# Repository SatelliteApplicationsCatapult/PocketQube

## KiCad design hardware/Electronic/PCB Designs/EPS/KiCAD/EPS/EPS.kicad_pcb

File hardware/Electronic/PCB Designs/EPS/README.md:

# PQ60 Electrical Power System

### At a glance
The current EPS design features the following basic systems:

1. Four _IXYS_ solar panels as a power source

2. Two _LTC3105_ based MPPT circuits to maximise the solar power generated

3. A _MAX8606ETD_ charge management IC to facilitate safe battery charging and effective system load management.

4. A regulation circuit including:
	* A watchdog timer to detect unresponsive MCUs (_STWD100PYW83F_)
	* A brownout monitor to detect invalid voltages (_BU4231G-TR_)
	* A 3V3 LDO regulator with active-high enable, allowing supervisor ICs or external MCUs to trigger a reset (_MIC5353-3.3YMT_)
	
5. Current monitoring:
	* _FAN4010IL6X_F113_ based high-side unidirectional current sense amplifier ICs to monitor solar output, total 3V3 draw and draw from the battery voltage line on the PQ60 bus
	* _INA211A_ based high-side bi-directional current sense amplifier to monitor total current draw and supply to the battery
	
6. Voltage monitoring:
	* Two MOSFET switched divider networks to measure the MPPT output voltage, the raw battery voltage
	* Direct measurement through MCU ADC of the 3V3 bus voltage
	
7. A 650mAh 3.7V single cell lithium polymer battery

8. Five high-side MOSFET (_NTA4151P & FK3303010L_) switched lines for the __PQ60__ standard, three 3V3 and two raw battery voltage. Each line is reverse polarity protected by the MOSFET and over current protected by a resettable polyfuse (_1206L025YR_)

9. A single _MKL02Z32VFM4_ 32 bit Kinetis MCU, for power management, current and voltage monitoring, line switching and communication with the OBC through I2C

### Usage
Will write something in this section once we actually have an EPS and some code to go with it. Maybe unnecessary if all dealt with through cube library? Will list maximum ratings, tolerances and so on.

### Current design
The current revision of the EPS board uses four __IXYS__ solar panels (_SLMD121H10L-ND_) as a power source, or can also be charged from a standard USB supply. The board contains two Maximum Power Point Tracker (MPPT) circuits based on the __LTC3105__ (_LTC3105EDD#PBF_) DC-DC switching boost regulator, sharing two panels each, with a low forward voltage drop schottkey diode to prevent reverse current leakage from the panels while not illuminated. The output of the MPPT circuits is fed through a twin channel MOSFET based ideal diode IC (_LTC4413_) to the charge management IC (_MAX8606ETD+T_). The total current produced by the MPPT circuits and delivered to the charging IC is monitored by a high side current sense amplifier (_FAN4010IL6X_), and the supply voltage can be measured through a resistor divider network. A MOSFET exists (_NX7002AK_) to disable this divider circuit to prevent current draw when not required. The charge management IC includes integrated load servicing. When the battery voltage exceeds 3.5V, the system output will be internally connected to the battery. Below this voltage, the power supply to the IC will first be used to service the system load, with the remaining available current being used to charge the battery. Both charging sources, the MPPTs and the USB supply, can be disabled if required, in order to obtain accurate battery voltage measurements. The MPPTs can be disabled through a signal to the SHDN input, and the USB supply is connected through a high side switched MOSFET circuit to enable disconnecting. The SHDN signal to the _LTC3105_ MPPTs is connected through an opto-isolator to allow recovery in the event of a fully discharged battery.

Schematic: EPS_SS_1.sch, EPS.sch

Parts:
C1, C2, C4, C5, C6, C8: 10uF; RESISTOR_C0603
C3, C7: 1uF; RESISTOR_C0402
IND1, IND2: WE-TPC-744031100; UBO_PQ60_WE-TPC-744031100
MPPT1, MPPT2: LTC3105; UBO_PQ60_DFN-3X3
R1, R4: 1.3M; RESISTOR_R0402
R2, R5: 330K; RESISTOR_R0402
R3, R6: 501K; RESISTOR_R0402
R33: 150R; RESISTOR_R0402
SOL1, SOL2, SOL3, SOL4: JST-B2B-ZH; UBO_PQ60_JST-B2B-ZR
U1: LTC4413EDDPBF; UBO_PQ60_DFN300X300X80-11N
U$4, U$10, U$14, U$17, U$31, U$32: BAT41; UBO_PQ60_SOD-123
U$24: EL3H7; UBO_PQ60_EL3H7

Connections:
GND: C1.2, C2.2, C3.2, C4.2, C5.2, C6.2, C7.2, C8.2, MPPT1.3 (FBLDO), MPPT1.EXP (GND), MPPT2.3 (FBLDO), MPPT2.EXP (GND), R2.1, R3.2, R5.1, R6.2, SOL1.P$1 (-), SOL2.P$1 (-), SOL3.P$1 (-), SOL4.P$1 (-), U1.2 (ENBA), U1.3 (GND), U1.4 (ENBB), U1.9 (STAT), U1.11 (EP), U$24.CATH (CATHODE), U$24.EMIT (EMITTER); also elsewhere on the board
MPPT1: C2.1, MPPT1.9 (VOUT), R1.2, U1.1 (INA)
MPPT2: C6.1, MPPT2.9 (VOUT), R4.2, U1.5 (INB)
MPPT_RAW: U1.6 (OUTB), U1.10 (OUTA); also elsewhere on the board
unnamed: IND1.P$1 (1), MPPT1.7 (SW)
unnamed: C1.1, IND1.P$3 (2), MPPT1.6 (VIN), U$31.P$1 (C), U$32.P$1 (C)
unnamed: IND2.P$1 (1), MPPT2.7 (SW)
unnamed: C3.1, MPPT1.10 (AUX)
unnamed: C7.1, MPPT2.10 (AUX)
unnamed: C5.1, IND2.P$3 (2), MPPT2.6 (VIN), U$14.P$1 (C), U$17.P$1 (C)
unnamed: MPPT2.1 (FB), R4.1, R5.2
unnamed: C4.1, MPPT1.2 (LDO)
unnamed: MPPT1.1 (FB), R1.1, R2.2
unnamed: MPPT2.5 (MPPC), R6.1
unnamed: C8.1, MPPT2.2 (LDO)
unnamed: MPPT2.4 (SHDN), U$10.P$2 (A)
unnamed: SOL4.P$2 (+), U$17.P$2 (A)
unnamed: MPPT1.4 (SHDN), U$4.P$2 (A)
unnamed: MPPT1.5 (MPPC), R3.1
unnamed: SOL3.P$2 (+), U$14.P$2 (A)
unnamed: SOL2.P$2 (+), U$31.P$2 (A)
unnamed: SOL1.P$2 (+), U$32.P$2 (A)
unnamed: R33.2, U$24.ANOD (ANODE)
OPTO: R33.1; also elsewhere on the board
SHDN: U$4.P$1 (C), U$10.P$1 (C), U$24.COLL (COLLECTOR)

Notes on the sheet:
10uH
501K --> 5.01V MPPV
1.004Vx((1.3M/330K)+1) =~4.959Vout
Maxmimu Power Point Tracking circuits, Opto-isolated charge disable and dual ideal diode outputs

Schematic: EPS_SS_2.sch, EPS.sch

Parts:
BAT56: JST-B2B-ZH; UBO_PQ60_JST-B2B-ZR
BU4331G-TR56: BU4231G-TR; EPS_PQ60_SSOP5
C21: 10nF; RESISTOR_C0402
C22: 1uF; RESISTOR_C0402
C23: 1nF; RESISTOR_C0402
INA210AIDCKT56: INA211A; UBO_PQ60_SC-70
PWR56: 961102-5604-AR; UBO_PQ60_961102-5604-AR
R7, R8, R9, R10, R15, R20, R21, R24, R28: 10K; RESISTOR_R0402
R13, R22, R36, R37: 0.15R, 1%; RESISTOR_R0603
R16: 2.2K; RESISTOR_R0402
R17: 3.3K; RESISTOR_R0402
R19: 0.015R 1%; RESISTOR_R0603
R40: 47K; RESISTOR_R0402
SJ1: UBO_PQ60_SJ
STWD100PYW83F56: STWD100PYW83F; UBO_PQ60_SOT_323-5
U9: TPS2553DRVT; UBO_PQ60_SON65P200X200X80-7N
U$2: BQ24079; UBO_PQ60_PVQFN16-THERM
U$15: PMV40UN2; UBO_PQ60_SOT23-3
U$18, U$19, U$25, U$26: FAN4010IL6X_F113; UBO_PQ60_FAN4010IL6X_F113
U$20: NCP706AMX300TAG; UBO_PQ60_XDFN8

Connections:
+3V3: INA210AIDCKT56.3 (VCC), R20.2, R36.2, U$25.6 (LOAD); also elsewhere on the board
+3V3_ISEN: R10.2, U$25.3 (IOUT); also elsewhere on the board
+3V3_REG: R36.1, R37.1, U$20.P$1 (OUT), U$20.P$2 (OUT), U$20.P$4 (SNS), U$25.1 (VIN), U$26.1 (VIN)
+3V3_SW: R37.2, U$26.6 (LOAD); also elsewhere on the board
+3V3_SW_ISEN: R9.2, U$26.3 (IOUT); also elsewhere on the board
BATV_BUS: R22.1, U$19.6 (LOAD); also elsewhere on the board
BAT_BUS_ISEN: R7.1, U$19.3 (IOUT); also elsewhere on the board
BAT_RAW_ISEN: INA210AIDCKT56.6 (OUT); also elsewhere on the board
BAT_RAW_ISEN_EN: U$15.1 (G); also elsewhere on the board
CHG_INPUT: R13.2, U$2.6 (EN1), U$2.13 (IN), U$18.6 (LOAD); also elsewhere on the board
EN: BU4331G-TR56.1 (VOUT), C23.1, R28.1, STWD100PYW83F56.1 (WDO), U9.4 (EN), U$20.P$6 (EN); also elsewhere on the board
GND: BAT56.P$1 (-), BU4331G-TR56.3 (GND), C21.2, C22.2, C23.2, INA210AIDCKT56.2 (GND), R7.2, R8.1, R9.1, R10.1, R15.1, R16.1, R17.1, R24.1, R40.1, STWD100PYW83F56.2 (GND), U9.5 (GND), U9.7 (EP), U$2.4 (CE), U$2.5 (EN2), U$2.7 (PGOOD), U$2.8 (VSS), U$2.9 (CHG), U$2.14 (TMR), U$2.15 (SYSOFF), U$2.17 (VSS), U$15.2 (S), U$18.5 (GND), U$19.5 (GND), U$20.P$5 (GND), U$20.P$9 (GND), U$25.5 (GND), U$26.5 (GND); also elsewhere on the board
MPPT_RAW: R13.1, U$18.1 (VIN); also elsewhere on the board
unnamed: INA210AIDCKT56.4 (IN+), R19.2, U$2.2 (BAT), U$2.3 (BAT)
unnamed: R15.2, U$2.1 (TS)
unnamed: R16.2, U$2.16 (ISET)
unnamed: R17.2, U$2.12 (ILIM)
unnamed: BAT56.P$2 (+), INA210AIDCKT56.5 (IN-), R19.1, R22.2, U$19.1 (VIN)
unnamed: R21.1, U$15.3 (D)
unnamed: INA210AIDCKT56.1 (REF), R20.1, R21.2
unnamed: BU4331G-TR56.5 (CT), C21.1
unnamed: R24.2, SJ1.2, STWD100PYW83F56.3 (EN)
unnamed: R40.2, U9.2 (ILIM)
SOL_ISEN: R8.2, U$18.3 (IOUT); also elsewhere on the board
SYS: PWR56.PIN2, U$2.10 (OUT), U$2.11 (OUT)
SYS_RAW: SJ1.1, U9.1 (OUT), U$20.P$7 (IN), U$20.P$8 (IN)
SYS_SW: BU4331G-TR56.2 (VDD), C22.1, PWR56.PIN1, R28.2, STWD100PYW83F56.5 (VCC), U9.6 (IN)
WDI: STWD100PYW83F56.4 (WDI); also elsewhere on the board

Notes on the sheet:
Panasonic ERJ3RSFR15V
200mA --> 3V
SUSUMU RR0816P-103-B-T5
VISHAY WSL0805R0300FEA
Total battery current monitoring
charge / discharge
INA210 200 gain 1.5V = A 3V = +500mA 0V = -500mA
Current monitoring on raw battery line
Main systems load
3v3 total bus load
~500mA limit
Watchdog timer Solder bridge to disable
Brownout monitor Vout high when valid voltage source detected
MOSFET load switch
3.0V 1.5A LDO
2.2K --> 405mA charge limit
3.3K --> 470mA input limit
Thermistor input

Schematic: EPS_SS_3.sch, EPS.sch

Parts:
C25, C26: 1uF; RESISTOR_C0402
FD1, FD2, FD3, FD4: FIDUCIAL; ADAFRUIT_FIDUCIAL_1MM
PQ60_HEADER56: FX8C-060P-SV2(92); OBC_FX8C-060P-SV(92)
PQ60_RECEPTACLE56: FX8C-060S-SV(92); TEMPLATE_FX8C-060S-SV(92)
R18, R25, R26, R27, R30: 10K; RESISTOR_R0402
TP1: TPTP07R; TESTPAD_TP07R
U10, U11, U12: TPS22960DCNR; UBO_PQ60_SOT65P280X145-8N
U$1, U$5, U$6, U$7: 3MMPILAR; UBO_PQ60_3MMPILAR
U$3, U$16, U$23, U$27, U$28: DEBUG-TP; UBO_PQ60_DEBUG-TP
U$8: ABS25_32.768KHZ; UBO_PQ60_ABS25
U$11, U$12: PMV40UN2; UBO_PQ60_SOT23-3
U$21: MKL02Z16VFM4; OBC_MKL02Z16VFM4
U$22: TAG_CONNECT; UBO_PQ60_TAG_CONNECT

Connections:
+3V3: C25.1, C26.1, PQ60_HEADER56.P$57, PQ60_HEADER56.P$58, PQ60_HEADER56.P$59, PQ60_HEADER56.P$60, PQ60_RECEPTACLE56.P$57, PQ60_RECEPTACLE56.P$58, PQ60_RECEPTACLE56.P$59, PQ60_RECEPTACLE56.P$60, U$3.P$1, U$21.3 (VDD), U$21.4 (VREFH), U$22.1 (VCC); also elsewhere on the board
+3V3_ISEN: U$21.16 (PTB0); also elsewhere on the board
+3V3_SW: U10.1 (VIN1), U10.4 (VIN2), U11.4 (VIN2); also elsewhere on the board
+3V3_SW1: PQ60_HEADER56.P$1, PQ60_HEADER56.P$2, PQ60_RECEPTACLE56.P$1, PQ60_RECEPTACLE56.P$2, U10.5 (VOUT2)
+3V3_SW1_EN: U10.3 (ON2), U$21.18 (PTB2)
+3V3_SW2: PQ60_HEADER56.P$5, PQ60_HEADER56.P$6, PQ60_RECEPTACLE56.P$5, PQ60_RECEPTACLE56.P$6, U10.8 (VOUT1)
+3V3_SW2_EN: U10.2 (ON1), U$21.19 (PTA8)
+3V3_SW3: PQ60_HEADER56.P$9, PQ60_HEADER56.P$10, PQ60_RECEPTACLE56.P$9, PQ60_RECEPTACLE56.P$10, U11.5 (VOUT2)
+3V3_SW3_EN: U11.3 (ON2), U$21.20 (PTA9)
+3V3_SW_ISEN: U$21.15 (PTA7); also elsewhere on the board
+5V_USB: PQ60_HEADER56.P$21, PQ60_HEADER56.P$22, PQ60_RECEPTACLE56.P$21, PQ60_RECEPTACLE56.P$22, R30.2, U12.1 (VIN1)
BATV_BUS: PQ60_HEADER56.P$49, PQ60_HEADER56.P$50, PQ60_HEADER56.P$51, PQ60_HEADER56.P$52, PQ60_RECEPTACLE56.P$49, PQ60_RECEPTACLE56.P$50, PQ60_RECEPTACLE56.P$51, PQ60_RECEPTACLE56.P$52, R18.2, U11.1 (VIN1), U12.4 (VIN2); also elsewhere on the board
BATV_SENS: R18.1, R25.2, U$21.25 (PTB5)
BATV_SENS_EN: U$11.1 (G), U$21.27 (PTA13)
BATV_SW1: PQ60_HEADER56.P$13, PQ60_HEADER56.P$14, PQ60_RECEPTACLE56.P$13, PQ60_RECEPTACLE56.P$14, U11.8 (VOUT1)
BATV_SW1_EN: U11.2 (ON1), U$21.21 (PTA10)
BATV_SW2: PQ60_HEADER56.P$17, PQ60_HEADER56.P$18, PQ60_RECEPTACLE56.P$17, PQ60_RECEPTACLE56.P$18, U12.5 (VOUT2)
BATV_SW2_EN: U12.3 (ON2), U$21.22 (PTA11)
BAT_BUS_ISEN: U$21.11 (PTB8); also elsewhere on the board
BAT_RAW_ISEN: U$21.12 (PTB9); also elsewhere on the board
BAT_RAW_ISEN_EN: U$21.14 (PTB11); also elsewhere on the board
CHG_INPUT: U12.8 (VOUT1); also elsewhere on the board
EN: PQ60_HEADER56.P$27, PQ60_RECEPTACLE56.P$27; also elsewhere on the board
EXTAL: U$8.1, U$21.7 (PTA3)
GND: C25.2, C26.2, PQ60_HEADER56.P$3, PQ60_HEADER56.P$4, PQ60_HEADER56.P$7, PQ60_HEADER56.P$8, PQ60_HEADER56.P$11, PQ60_HEADER56.P$12, PQ60_HEADER56.P$15, PQ60_HEADER56.P$16, PQ60_HEADER56.P$19, PQ60_HEADER56.P$20, PQ60_HEADER56.P$23, PQ60_HEADER56.P$24, PQ60_HEADER56.P$28, PQ60_HEADER56.P$45, PQ60_HEADER56.P$46, PQ60_HEADER56.P$47, PQ60_HEADER56.P$48, PQ60_HEADER56.P$53, PQ60_HEADER56.P$54, PQ60_HEADER56.P$55, PQ60_HEADER56.P$56, PQ60_RECEPTACLE56.P$3, PQ60_RECEPTACLE56.P$4, PQ60_RECEPTACLE56.P$7, PQ60_RECEPTACLE56.P$8, PQ60_RECEPTACLE56.P$11, PQ60_RECEPTACLE56.P$12, PQ60_RECEPTACLE56.P$15, PQ60_RECEPTACLE56.P$16, PQ60_RECEPTACLE56.P$19, PQ60_RECEPTACLE56.P$20, PQ60_RECEPTACLE56.P$23, PQ60_RECEPTACLE56.P$24, PQ60_RECEPTACLE56.P$28, PQ60_RECEPTACLE56.P$45, PQ60_RECEPTACLE56.P$46, PQ60_RECEPTACLE56.P$47, PQ60_RECEPTACLE56.P$48, PQ60_RECEPTACLE56.P$53, PQ60_RECEPTACLE56.P$54, PQ60_RECEPTACLE56.P$55, PQ60_RECEPTACLE56.P$56, U10.6 (GND), U11.6 (GND), U12.6 (GND), U$1.P$1, U$5.P$1, U$6.P$1, U$7.P$1, U$11.2 (S), U$12.2 (S), U$21.5 (VREFL), U$21.6 (VSS), U$21.GND@ (VSS), U$22.5 (GND), U$23.P$1; also elsewhere on the board
GPIO0: PQ60_HEADER56.P$25, PQ60_RECEPTACLE56.P$25, U$21.17 (PTB1)
GPIO1: PQ60_HEADER56.P$26, PQ60_RECEPTACLE56.P$26
GPIO2: PQ60_HEADER56.P$34, PQ60_RECEPTACLE56.P$34
GPIO3: PQ60_HEADER56.P$35, PQ60_RECEPTACLE56.P$35
GPIO4: PQ60_HEADER56.P$36, PQ60_RECEPTACLE56.P$36
GPIO5: PQ60_HEADER56.P$37, PQ60_RECEPTACLE56.P$37
GPIO6: PQ60_HEADER56.P$38, PQ60_RECEPTACLE56.P$38
GPIO7: PQ60_HEADER56.P$39, PQ60_RECEPTACLE56.P$39
GPIO8: PQ60_HEADER56.P$40, PQ60_RECEPTACLE56.P$40
GPIO9: PQ60_HEADER56.P$41, PQ60_RECEPTACLE56.P$41
GPIO10: PQ60_HEADER56.P$42, PQ60_RECEPTACLE56.P$42
GPIO11: PQ60_HEADER56.P$43, PQ60_RECEPTACLE56.P$43
GPIO12: PQ60_HEADER56.P$44, PQ60_RECEPTACLE56.P$44
MISO: PQ60_HEADER56.P$32, PQ60_RECEPTACLE56.P$32
MOSI: PQ60_HEADER56.P$31, PQ60_RECEPTACLE56.P$31
MPPTV_SENS: R26.1, R27.2, U$21.26 (PTA12)
MPPTV_SENS_EN: U$12.1 (G), U$21.28 (PTB12)
MPPT_RAW: R26.2; also elsewhere on the board
unnamed: TP1.TP, U$21.2 (PTB7)
unnamed: R25.1, U$11.3 (D)
unnamed: R27.1, U$12.3 (D)
OPTO: U$21.1 (PTB6); also elsewhere on the board
SCK: PQ60_HEADER56.P$33, PQ60_RECEPTACLE56.P$33
SCL: PQ60_HEADER56.P$29, PQ60_RECEPTACLE56.P$29, U$21.23 (PTB3)
SDA: PQ60_HEADER56.P$30, PQ60_RECEPTACLE56.P$30, U$21.24 (PTB4)
SOL_ISEN: U$21.13 (PTB10); also elsewhere on the board
SWDCLK: U$21.30 (PTA0), U$22.4 (CLK), U$27.P$1
SWDIO: U$21.32 (PTA2), U$22.2 (DIO), U$28.P$1
SWDRST: U$16.P$1, U$21.31 (PTA1), U$22.3 (RST)
USB_DISCONNECT: R30.1, U12.2 (ON1), U$21.9 (PTA5)
WDI: U$21.10 (PTA6); also elsewhere on the board
XTAL: U$8.4, U$21.8 (PTA4)

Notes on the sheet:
Fiducial markers

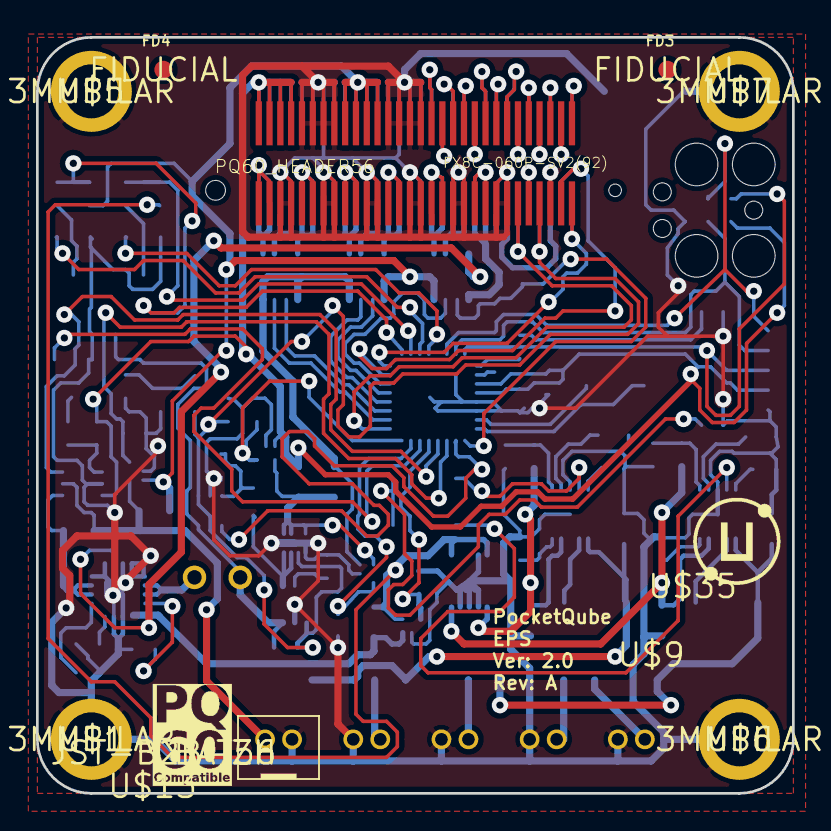
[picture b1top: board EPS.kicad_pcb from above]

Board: 2 copper layers, 42.0 x 42.0 mm, 99 parts (0 on the bottom side), 92 nets.

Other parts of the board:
U$9: SA_LOGO_SMALL
U$13: PQ60_CMP
U$35: UBO_LOGO

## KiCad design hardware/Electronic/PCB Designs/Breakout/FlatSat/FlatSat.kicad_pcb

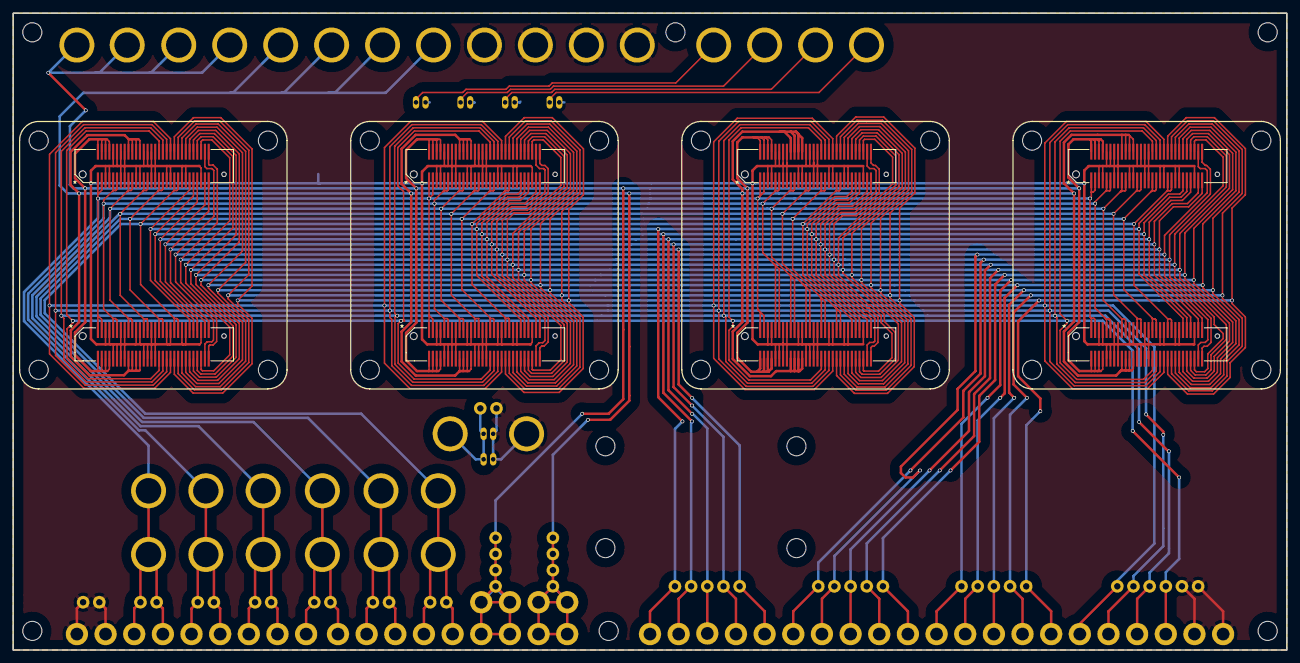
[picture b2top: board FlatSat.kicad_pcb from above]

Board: 2 copper layers, 200.0 x 100.0 mm, 158 parts (0 on the bottom side), 33 nets.

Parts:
H1, H2, H3, H4, H9, H10, H27, H28, H29, H30, H31, H32, H37, H38, H51, H52, H53, H54, H55, H56, H61, H62, H68, H70, H72, H74, H75, H76, H82, H84, H86, H88, H89, H92, H93, H96, H97, H100, H104, H105, H108, H109, H112: test_probe_hook_2mm; test_probe_2mm
H5, H6, H7, H8, H11, H12, H23, H24, H25, H26, H33, H34, H39, H40, H47, H48, H49, H50, H57, H58, H63, H64, H67, H69, H71, H73, H77, H78, H81, H83, H85, H87, H90, H91, H94, H95, H98, H99, H103, H106, H107, H110, H111, H119, H121: pin_hdr_std_2.54mm
H13, H14, H15, H16, H17, H18, H19, H20, H21, H22, H35, H36, H41, H42, H43, H44, H45, H46, H59, H60, H65, H66, H79, H80, H101, H113, H115, H117, H123, H124: banana_direct_4mm
H102, H114, H116, H118, H120, H122: JST_ZH; JST_ZH_B2B
J1, J2, J3, J4: FX8C-060P
J5, J6, J7, J8: FX8C-060S
SMD: pcb_standoff_mount
SMD#2, SMD#3, SMD#4, SMD#5, SMD#6, SMD#7, SMD#8, SMD#9, SMD#10, SMD#11, SMD#12, SMD#13, SMD#14, SMD#15, SMD#16, SMD#17, SMD#18, SMD#19, SMD#20, SMD#21, SMD#22, SMD#23, SMD#24, SMD#25, SMD#26: pcb_standoff_mount

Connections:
/P1: H9.1, H10.1, H11.1, H12.1, H13.1, H14.1, J1.1, J1.2, J2.1, J2.2, J3.1, J3.2, J4.1, J4.2, J5.1, J5.2, J6.1, J6.2, J7.1, J7.2, J8.1, J8.2
/P5: H31.1, H32.1, H33.1, H34.1, H35.1, H36.1, J1.5, J1.6, J2.5, J2.6, J3.5, J3.6, J4.5, J4.6, J5.5, J5.6, J6.5, J6.6, J7.5, J7.6, J8.5, J8.6
/P10: H37.1, H38.1, H39.1, H40.1, H41.1, H42.1, J1.9, J1.10, J2.9, J2.10, J3.9, J3.10, J4.9, J4.10, J5.9, J5.10, J6.9, J6.10, J7.9, J7.10, J8.9, J8.10
/P13: H55.1, H56.1, H57.1, H58.1, H59.1, H60.1, J1.13, J1.14, J2.13, J2.14, J3.13, J3.14, J4.13, J4.14, J5.13, J5.14, J6.13, J6.14, J7.13, J7.14, J8.13, J8.14
/P17: H61.1, H62.1, H63.1, H64.1, H65.1, H66.1, J1.17, J1.18, J2.17, J2.18, J3.17, J3.18, J4.17, J4.18, J5.17, J5.18, J6.17, J6.18, J7.17, J7.18, J8.17, J8.18
/P21: H75.1, H76.1, H77.1, H78.1, H79.1, H80.1, J1.21, J1.22, J2.21, J2.22, J3.21, J3.22, J4.21, J4.22, J5.21, J5.22, J6.21, J6.22, J7.21, J7.22, J8.21, J8.22
/P25: H89.1, H90.1, J1.25, J2.25, J3.25, J4.25, J5.25, J6.25, J7.25, J8.25
/P26: H93.1, H94.1, J1.26, J2.26, J3.26, J4.26, J5.26, J6.26, J7.26, J8.26
/P27: H97.1, H98.1, J1.27, J2.27, J3.27, J4.27, J5.27, J6.27, J7.27, J8.27
/P29: H105.1, H106.1, J1.29, J2.29, J3.29, J4.29, J5.29, J6.29, J7.29, J8.29
/P30: H109.1, H110.1, J1.30, J2.30, J3.30, J4.30, J5.30, J6.30, J7.30, J8.30
/P31: H111.1, H112.1, J1.31, J2.31, J3.31, J4.31, J5.31, J6.31, J7.31, J8.31
/P32: H107.1, H108.1, J1.32, J2.32, J3.32, J4.32, J5.32, J6.32, J7.32, J8.32
/P33: H103.1, H104.1, J1.33, J2.33, J3.33, J4.33, J5.33, J6.33, J7.33, J8.33
/P34: H99.1, H100.1, J1.34, J2.34, J3.34, J4.34, J5.34, J6.34, J7.34, J8.34
/P35: H95.1, H96.1, J1.35, J2.35, J3.35, J4.35, J5.35, J6.35, J7.35, J8.35
/P36: H91.1, H92.1, J1.36, J2.36, J3.36, J4.36, J5.36, J6.36, J7.36, J8.36
/P37: H87.1, H88.1, J1.37, J2.37, J3.37, J4.37, J5.37, J6.37, J7.37, J8.37
/P38: H85.1, H86.1, J1.38, J2.38, J3.38, J4.38, J5.38, J6.38, J7.38, J8.38
/P39: H83.1, H84.1, J1.39, J2.39, J3.39, J4.39, J5.39, J6.39, J7.39, J8.39
/P40: H81.1, H82.1, J1.40, J2.40, J3.40, J4.40, J5.40, J6.40, J7.40, J8.40
/P41: H73.1, H74.1, J1.41, J2.41, J3.41, J4.41, J5.41, J6.41, J7.41, J8.41
/P42: H71.1, H72.1, J1.42, J2.42, J3.42, J4.42, J5.42, J6.42, J7.42, J8.42
/P43: H69.1, H70.1, J1.43, J2.43, J3.43, J4.43, J5.43, J6.43, J7.43, J8.43
/P44: H67.1, H68.1, J1.44, J2.44, J3.44, J4.44, J5.44, J6.44, J7.44, J8.44
/P49: H43.1, H44.1, H45.1, H46.1, H47.1, H48.1, H49.1, H50.1, H51.1, H52.1, H53.1, H54.1, J1.49, J1.50, J1.51, J1.52, J2.49, J2.50, J2.51, J2.52, J3.49, J3.50, J3.51, J3.52, J4.49, J4.50, J4.51, J4.52, J5.49, J5.50, J5.51, J5.52, J6.49, J6.50, J6.51, J6.52, J7.49, J7.50, J7.51, J7.52, J8.49, J8.50, J8.51, J8.52
/P57: H19.1, H20.1, H21.1, H22.1, H23.1, H24.1, H25.1, H26.1, H27.1, H28.1, H29.1, H30.1, J1.57, J1.58, J1.59, J1.60, J2.57, J2.58, J2.59, J2.60, J3.57, J3.58, J3.59, J3.60, J4.57, J4.58, J4.59, J4.60, J5.57, J5.58, J5.59, J5.60, J6.57, J6.58, J6.59, J6.60, J7.57, J7.58, J7.59, J7.60, J8.57, J8.58, J8.59, J8.60
GND: H1.1, H2.1, H3.1, H4.1, H5.1, H6.1, H7.1, H8.1, H15.1, H16.1, H17.1, H18.1, H102.2, H114.2, H116.2, H118.2, H120.2, H121.1, H122.2, H124.1, J1.3, J1.4, J1.7, J1.8, J1.11, J1.12, J1.15, J1.16, J1.19, J1.20, J1.23, J1.24, J1.28, J1.45, J1.46, J1.47, J1.48, J1.53, J1.54, J1.55, J1.56, J2.3, J2.4, J2.7, J2.8, J2.11, J2.12, J2.15, J2.16, J2.19, J2.20, J2.23, J2.24, J2.28, J2.45, J2.46, J2.47, J2.48, J2.53, J2.54, J2.55, J2.56, J3.3, J3.4, J3.7, J3.8, J3.11, J3.12, J3.15, J3.16, J3.19, J3.20, J3.23, J3.24, J3.28, J3.45, J3.46, J3.47, J3.48, J3.53, J3.54, J3.55, J3.56, J4.3, J4.4, J4.7, J4.8, J4.11, J4.12, J4.15, J4.16, J4.19, J4.20, J4.23, J4.24, J4.28, J4.45, J4.46, J4.47, J4.48, J4.53, J4.54, J4.55, J4.56, J5.3, J5.4, J5.7, J5.8, J5.11, J5.12, J5.15, J5.16, J5.19, J5.20, J5.23, J5.24, J5.28, J5.45, J5.46, J5.47, J5.48, J5.53, J5.54, J5.55, J5.56, J6.3, J6.4, J6.7, J6.8, J6.11, J6.12, J6.15, J6.16, J6.19, J6.20, J6.23, J6.24, J6.28, J6.45, J6.46, J6.47, J6.48, J6.53, J6.54, J6.55, J6.56, J7.3, J7.4, J7.7, J7.8, J7.11, J7.12, J7.15, J7.16, J7.19, J7.20, J7.23, J7.24, J7.28, J7.45, J7.46, J7.47, J7.48, J7.53, J7.54, J7.55, J7.56, J8.3, J8.4, J8.7, J8.8, J8.11, J8.12, J8.15, J8.16, J8.19, J8.20, J8.23, J8.24, J8.28, J8.45, J8.46, J8.47, J8.48, J8.53, J8.54, J8.55, J8.56
unnamed: H101.1, H102.1
unnamed: H113.1, H114.1
unnamed: H115.1, H116.1
unnamed: H117.1, H118.1
unnamed: H119.1, H120.1, H122.1, H123.1

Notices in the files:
hardware/Electronic/PCB Designs/EPS/KiCAD/EPS/EPS.kicad_pcb:
Copyright 2016 Satellite Applications Catapult
